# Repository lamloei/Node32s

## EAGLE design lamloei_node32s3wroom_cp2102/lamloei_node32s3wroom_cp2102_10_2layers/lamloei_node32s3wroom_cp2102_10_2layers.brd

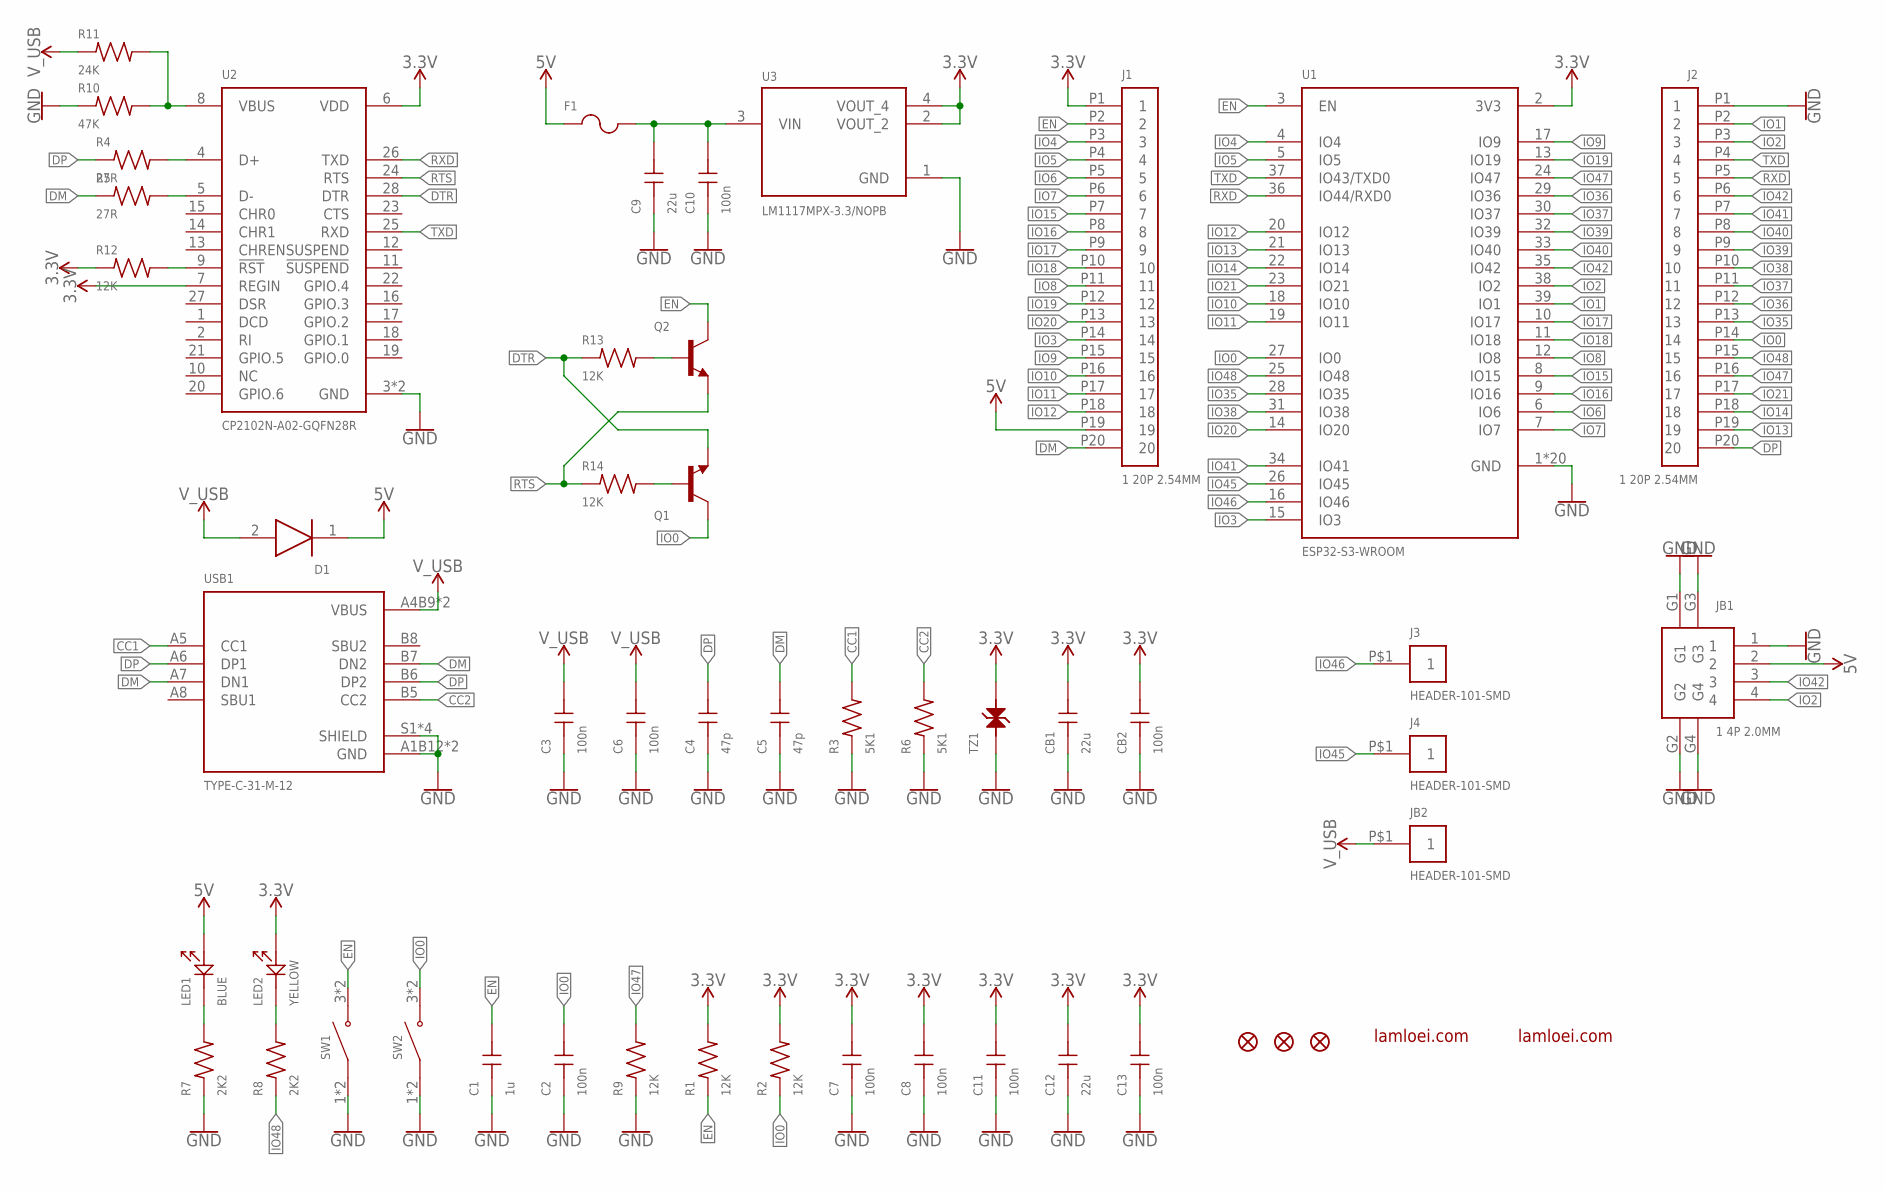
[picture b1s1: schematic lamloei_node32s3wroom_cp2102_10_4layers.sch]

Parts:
C1: 1u; GRM155R70J105KA12D
C2, C3, C6, C7, C8, C10, C11, C13: 100n; GCM155R71H104KE02D
C4, C5: 47p; GCM1555C1H470JA16D
C9, C12: 22u; GCM21BR71H105KA03L
CB1: 22u; GCM21BR71H105KA03L
CB2: 100n; GCM155R71H104KE02D
D1: PMEG4050EP,115
F1: MF-NSMF050-2
J1, J2: 1 20P 2.54MM; HEADER-120
J3, J4: HEADER-101-SMD
JB1: 1 4P 2.0MM; A2012WR-S-4P
JB2: HEADER-101-SMD
LED1: BLUE; 19-217BHC-ZL1M2RY3T
LED2: YELLOW; 19-213/Y2C-CQ2R2L/3T(CY)
Q1, Q2: BC847B,215
R1, R2, R9, R12, R13, R14: 12K; R0402
R3, R6: 5K1; R0402
R4, R5: 27R; R0402
R7, R8: 2K2; R0402
R10: 47K; R0402
R11: 24K; R0402
SW1, SW2: K2-1808SN-A4SW-01
TZ1: LXES15AAA1-153
U1: ESP32-S3-WROOM
U2: CP2102N-A02-GQFN28R
U3: LM1117MPX-3.3/NOPB
USB1: TYPE-C-31-M-12
ZFD1, ZFD2, ZFD3: FIDUCIAL1X2; FIDUCIAL-1X2
ZL1, ZL2: LAMLEOI_LOGO_3

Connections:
3.3V: C7.2, C8.2, C11.2, C12.2, C13.2, CB1.2, CB2.2, J1.P1 (1), LED2.2, R1.2, R2.2, R12.1, TZ1.2, U1.2 (3V3), U2.6 (VDD), U2.7 (REGIN), U3.2 (VOUT_2), U3.4 (VOUT_4); also elsewhere on the board
5V: D1.1 (K), F1.1, J1.P19 (19), JB1.2, LED1.2; also elsewhere on the board
CC1: R3.2, USB1.A5 (CC1)
CC2: R6.2, USB1.B5 (CC2)
DM: C5.2, J1.P20 (20), R5.1, USB1.A7 (DN1), USB1.B7 (DN2); also elsewhere on the board
DP: C4.2, J2.P20 (20), R4.1, USB1.A6 (DP1), USB1.B6 (DP2); also elsewhere on the board
DTR: Q1.E, R13.1, U2.28 (DTR)
EN: C1.2, J1.P2 (2), Q2.C, R1.1, SW1.3 (NO), SW1.4 (NO), U1.3 (EN); also elsewhere on the board
GND: C1.1, C2.1, C3.1, C4.1, C5.1, C6.1, C7.1, C8.1, C9.1, C10.1, C11.1, C12.1, C13.1, CB1.1, CB2.1, J2.P1 (1), JB1.1, JB1.G1, JB1.G2, JB1.G3, JB1.G4, R3.1, R6.1, R7.1, R9.1, R10.1, SW1.1 (COM), SW1.2 (COM), SW2.1 (COM), SW2.2 (COM), TZ1.1, U1.1 (GND), U1.1.1 (GND), U1.1.2 (GND), U1.1.3 (GND), U1.1.4 (GND), U1.1.5 (GND), U1.1.6 (GND), U1.1.7 (GND), U1.1.8 (GND), U1.1.9 (GND), U1.1.10 (GND), U1.1.11 (GND), U1.1.12 (GND), U1.1.13 (GND), U1.1.14 (GND), U1.1.15 (GND), U1.1.16 (GND), U1.1.17 (GND), U1.1.18 (GND), U1.40 (GND), U2.3 (GND), U2.29 (GND), U3.1 (GND), USB1.A1B12 (GND), USB1.B1A12 (GND), USB1.S1 (SHIELD), USB1.S2 (SHIELD), USB1.S3 (SHIELD), USB1.S4 (SHIELD); also elsewhere on the board
GPIO.5: U2.21 (GPIO.5)
IO0: C2.2, J2.P14 (14), Q1.C, R2.1, SW2.3 (NO), SW2.4 (NO), U1.27 (IO0); also elsewhere on the board
IO1: J2.P2 (2), U1.39 (IO1); also elsewhere on the board
IO2: J2.P3 (3), JB1.4, U1.38 (IO2); also elsewhere on the board
IO3: J1.P14 (14), U1.15 (IO3); also elsewhere on the board
IO4: J1.P3 (3), U1.4 (IO4); also elsewhere on the board
IO5: J1.P4 (4), U1.5 (IO5); also elsewhere on the board
IO6: J1.P5 (5), U1.6 (IO6); also elsewhere on the board
IO7: J1.P6 (6), U1.7 (IO7); also elsewhere on the board
IO8: J1.P11 (11), U1.12 (IO8); also elsewhere on the board
IO9: J1.P15 (15), U1.17 (IO9); also elsewhere on the board
IO10: J1.P16 (16), U1.18 (IO10); also elsewhere on the board
IO11: J1.P17 (17), U1.19 (IO11); also elsewhere on the board
IO12: J1.P18 (18), U1.20 (IO12); also elsewhere on the board
IO13: J2.P19 (19), U1.21 (IO13); also elsewhere on the board
IO14: J2.P18 (18), U1.22 (IO14); also elsewhere on the board
IO15: J1.P7 (7), U1.8 (IO15); also elsewhere on the board
IO16: J1.P8 (8), U1.9 (IO16); also elsewhere on the board
IO17: J1.P9 (9), U1.10 (IO17); also elsewhere on the board
IO18: J1.P10 (10), U1.11 (IO18); also elsewhere on the board
IO19: J1.P12 (12), U1.13 (IO19); also elsewhere on the board
IO20: J1.P13 (13), U1.14 (IO20); also elsewhere on the board
IO21: J2.P17 (17), U1.23 (IO21); also elsewhere on the board
IO35: J2.P13 (13), U1.28 (IO35); also elsewhere on the board
IO36: J2.P12 (12), U1.29 (IO36); also elsewhere on the board
IO37: J2.P11 (11), U1.30 (IO37); also elsewhere on the board
IO38: J2.P10 (10), U1.31 (IO38); also elsewhere on the board
IO39: J2.P9 (9), U1.32 (IO39); also elsewhere on the board
IO40: J2.P8 (8), U1.33 (IO40); also elsewhere on the board
IO41: J2.P7 (7), U1.34 (IO41); also elsewhere on the board
IO42: J2.P6 (6), JB1.3, U1.35 (IO42); also elsewhere on the board
IO45: J4.P$1, U1.26 (IO45)
IO46: J3.P$1, U1.16 (IO46)
IO47: J2.P16 (16), R9.2, U1.24 (IO47); also elsewhere on the board
IO48: J2.P15 (15), R8.1, U1.25 (IO48); also elsewhere on the board
unnamed: R5.2, U2.5 (D-)
unnamed: R4.2, U2.4 (D+)
unnamed: C9.2, C10.2, F1.2, U3.3 (VIN)
unnamed: LED1.1, R7.2
unnamed: LED2.1, R8.2
unnamed: Q2.B, R13.2
unnamed: Q1.B, R14.2
unnamed: R12.2, U2.9 (!RST)
unnamed: R10.2, R11.2, U2.8 (VBUS)
RTS: Q2.E, R14.1, U2.24 (RTS)
RXD: J2.P5 (5), U1.36 (IO44/RXD0), U2.26 (TXD); also elsewhere on the board
TXD: J2.P4 (4), U1.37 (IO43/TXD0), U2.25 (RXD); also elsewhere on the board
V_USB: C3.2, C6.2, D1.2 (A), JB2.P$1, R11.1, USB1.A4B9 (VBUS), USB1.B4A9 (VBUS)

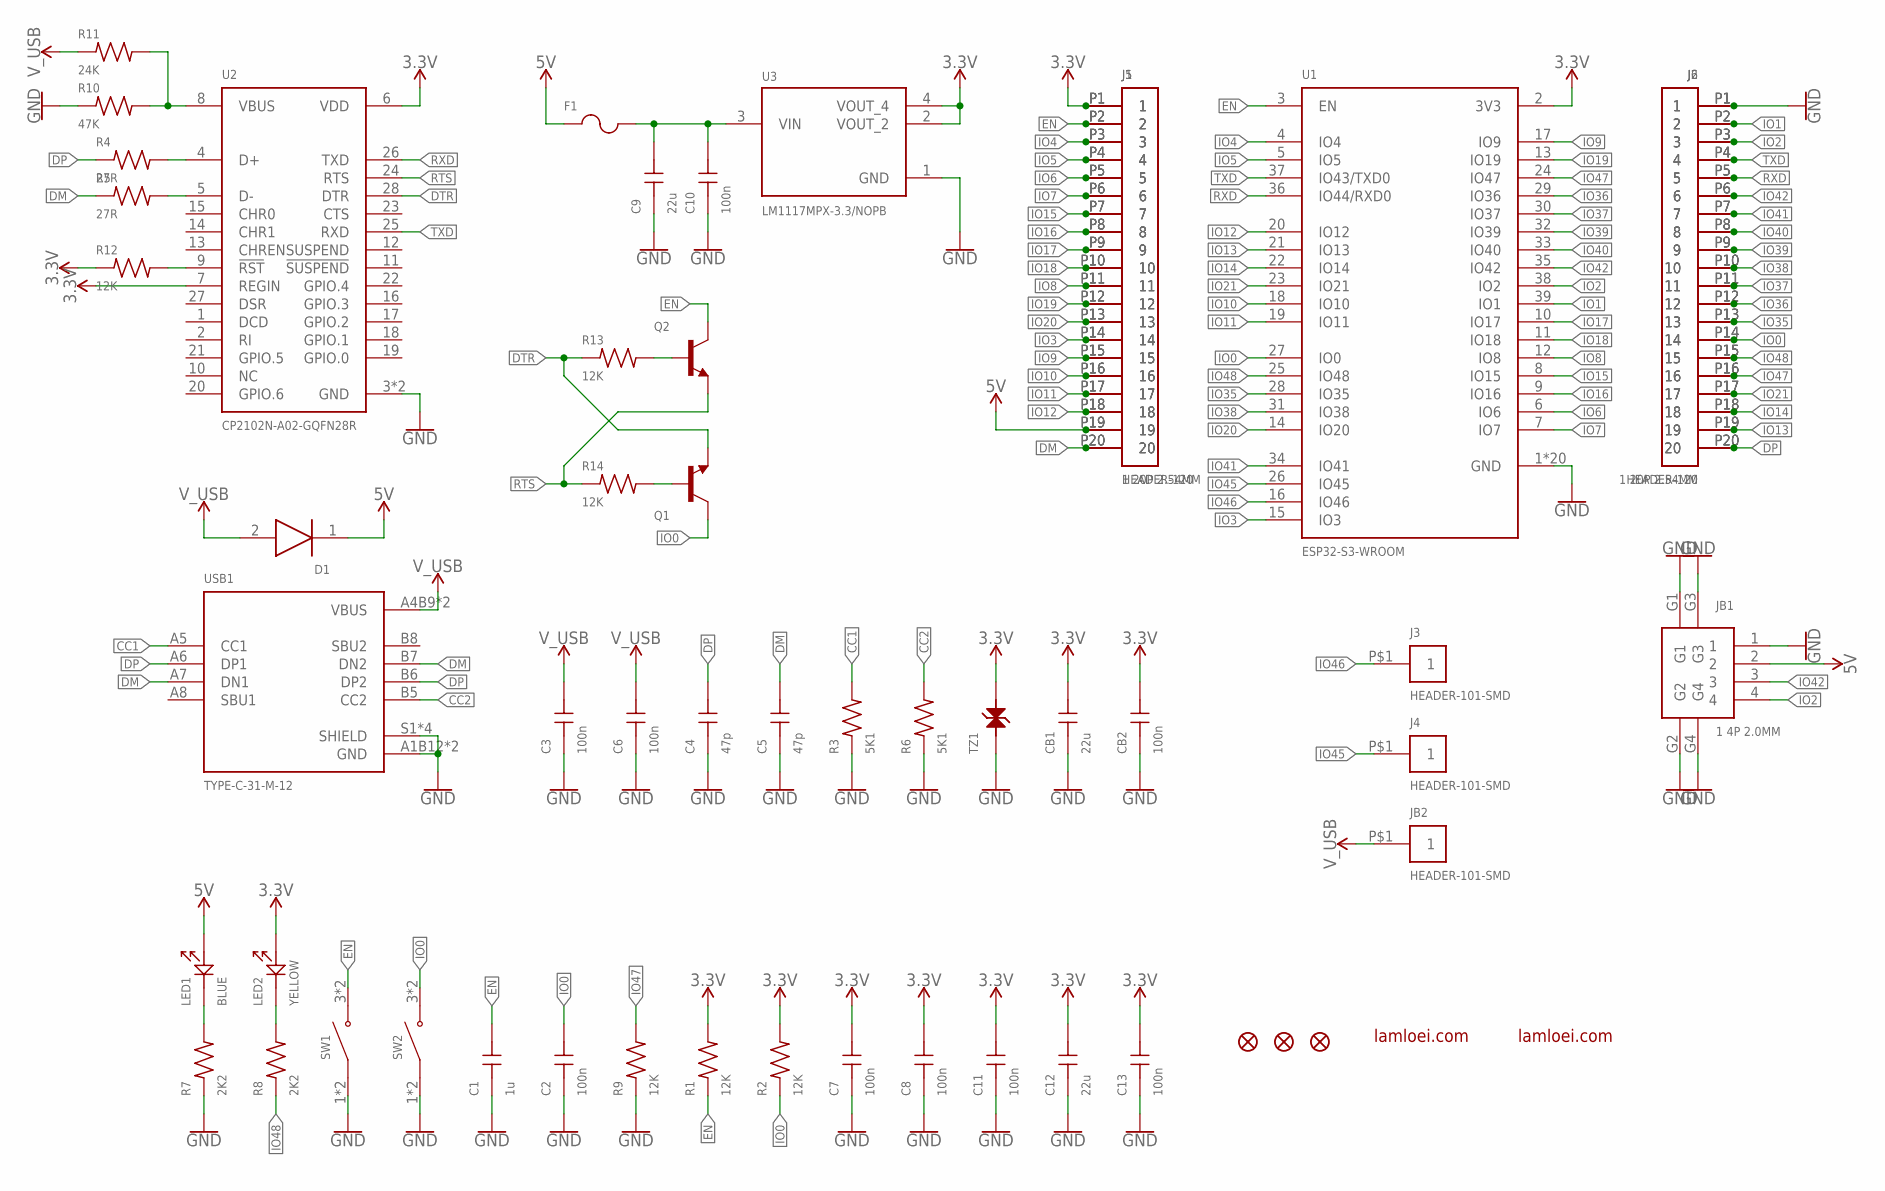
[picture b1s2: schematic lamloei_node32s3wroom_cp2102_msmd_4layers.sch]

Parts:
C1: 1u; GRM155R70J105KA12D
C2, C3, C6, C7, C8, C10, C11, C13: 100n; GCM155R71H104KE02D
C4, C5: 47p; GCM1555C1H470JA16D
C9, C12: 22u; GCM21BR71H105KA03L
CB1: 22u; GCM21BR71H105KA03L
CB2: 100n; GCM155R71H104KE02D
D1: PMEG4050EP,115
F1: MF-NSMF050-2
J1, J2: 1 20P 2.54MM; HEADER-120
J3, J4: HEADER-101-SMD
J5, J6: HEADER-120
JB1: 1 4P 2.0MM; A2012WR-S-4P
JB2: HEADER-101-SMD
LED1: BLUE; 19-217BHC-ZL1M2RY3T
LED2: YELLOW; 19-213/Y2C-CQ2R2L/3T(CY)
Q1, Q2: BC847B,215
R1, R2, R9, R12, R13, R14: 12K; R0402
R3, R6: 5K1; R0402
R4, R5: 27R; R0402
R7, R8: 2K2; R0402
R10: 47K; R0402
R11: 24K; R0402
SW1, SW2: K2-1808SN-A4SW-01
TZ1: LXES15AAA1-153
U1: ESP32-S3-WROOM
U2: CP2102N-A02-GQFN28R
U3: LM1117MPX-3.3/NOPB
USB1: TYPE-C-31-M-12
ZFD1, ZFD2, ZFD3: FIDUCIAL1X2; FIDUCIAL-1X2
ZL1, ZL2: LAMLEOI_LOGO_3

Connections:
3.3V: C7.2, C8.2, C11.2, C12.2, C13.2, CB1.2, CB2.2, J1.P1 (1), J5.P1 (1), LED2.2, R1.2, R2.2, R12.1, TZ1.2, U1.2 (3V3), U2.6 (VDD), U2.7 (REGIN), U3.2 (VOUT_2), U3.4 (VOUT_4)
5V: D1.1 (K), F1.1, J1.P19 (19), J5.P19 (19), JB1.2, LED1.2
CC1: R3.2, USB1.A5 (CC1)
CC2: R6.2, USB1.B5 (CC2)
DM: C5.2, J1.P20 (20), J5.P20 (20), R5.1, USB1.A7 (DN1), USB1.B7 (DN2)
DP: C4.2, J2.P20 (20), J6.P20 (20), R4.1, USB1.A6 (DP1), USB1.B6 (DP2)
DTR: Q1.E, R13.1, U2.28 (DTR)
EN: C1.2, J1.P2 (2), J5.P2 (2), Q2.C, R1.1, SW1.3 (NO), SW1.4 (NO), U1.3 (EN)
GND: C1.1, C2.1, C3.1, C4.1, C5.1, C6.1, C7.1, C8.1, C9.1, C10.1, C11.1, C12.1, C13.1, CB1.1, CB2.1, J2.P1 (1), J6.P1 (1), JB1.1, JB1.G1, JB1.G2, JB1.G3, JB1.G4, R3.1, R6.1, R7.1, R9.1, R10.1, SW1.1 (COM), SW1.2 (COM), SW2.1 (COM), SW2.2 (COM), TZ1.1, U1.1 (GND), U1.1.1 (GND), U1.1.2 (GND), U1.1.3 (GND), U1.1.4 (GND), U1.1.5 (GND), U1.1.6 (GND), U1.1.7 (GND), U1.1.8 (GND), U1.1.9 (GND), U1.1.10 (GND), U1.1.11 (GND), U1.1.12 (GND), U1.1.13 (GND), U1.1.14 (GND), U1.1.15 (GND), U1.1.16 (GND), U1.1.17 (GND), U1.1.18 (GND), U1.40 (GND), U2.3 (GND), U2.29 (GND), U3.1 (GND), USB1.A1B12 (GND), USB1.B1A12 (GND), USB1.S1 (SHIELD), USB1.S2 (SHIELD), USB1.S3 (SHIELD), USB1.S4 (SHIELD)
GPIO.5: U2.21 (GPIO.5)
IO0: C2.2, J2.P14 (14), J6.P14 (14), Q1.C, R2.1, SW2.3 (NO), SW2.4 (NO), U1.27 (IO0)
IO1: J2.P2 (2), J6.P2 (2), U1.39 (IO1)
IO2: J2.P3 (3), J6.P3 (3), JB1.4, U1.38 (IO2)
IO3: J1.P14 (14), J5.P14 (14), U1.15 (IO3)
IO4: J1.P3 (3), J5.P3 (3), U1.4 (IO4)
IO5: J1.P4 (4), J5.P4 (4), U1.5 (IO5)
IO6: J1.P5 (5), J5.P5 (5), U1.6 (IO6)
IO7: J1.P6 (6), J5.P6 (6), U1.7 (IO7)
IO8: J1.P11 (11), J5.P11 (11), U1.12 (IO8)
IO9: J1.P15 (15), J5.P15 (15), U1.17 (IO9)
IO10: J1.P16 (16), J5.P16 (16), U1.18 (IO10)
IO11: J1.P17 (17), J5.P17 (17), U1.19 (IO11)
IO12: J1.P18 (18), J5.P18 (18), U1.20 (IO12)
IO13: J2.P19 (19), J6.P19 (19), U1.21 (IO13)
IO14: J2.P18 (18), J6.P18 (18), U1.22 (IO14)
IO15: J1.P7 (7), J5.P7 (7), U1.8 (IO15)
IO16: J1.P8 (8), J5.P8 (8), U1.9 (IO16)
IO17: J1.P9 (9), J5.P9 (9), U1.10 (IO17)
IO18: J1.P10 (10), J5.P10 (10), U1.11 (IO18)
IO19: J1.P12 (12), J5.P12 (12), U1.13 (IO19)
IO20: J1.P13 (13), J5.P13 (13), U1.14 (IO20)
IO21: J2.P17 (17), J6.P17 (17), U1.23 (IO21)
IO35: J2.P13 (13), J6.P13 (13), U1.28 (IO35)
IO36: J2.P12 (12), J6.P12 (12), U1.29 (IO36)
IO37: J2.P11 (11), J6.P11 (11), U1.30 (IO37)
IO38: J2.P10 (10), J6.P10 (10), U1.31 (IO38)
IO39: J2.P9 (9), J6.P9 (9), U1.32 (IO39)
IO40: J2.P8 (8), J6.P8 (8), U1.33 (IO40)
IO41: J2.P7 (7), J6.P7 (7), U1.34 (IO41)
IO42: J2.P6 (6), J6.P6 (6), JB1.3, U1.35 (IO42)
IO45: J4.P$1, U1.26 (IO45)
IO46: J3.P$1, U1.16 (IO46)
IO47: J2.P16 (16), J6.P16 (16), R9.2, U1.24 (IO47)
IO48: J2.P15 (15), J6.P15 (15), R8.1, U1.25 (IO48)
unnamed: R5.2, U2.5 (D-)
unnamed: R4.2, U2.4 (D+)
unnamed: C9.2, C10.2, F1.2, U3.3 (VIN)
unnamed: LED1.1, R7.2
unnamed: LED2.1, R8.2
unnamed: Q2.B, R13.2
unnamed: Q1.B, R14.2
unnamed: R12.2, U2.9 (!RST)
unnamed: R10.2, R11.2, U2.8 (VBUS)
RTS: Q2.E, R14.1, U2.24 (RTS)
RXD: J2.P5 (5), J6.P5 (5), U1.36 (IO44/RXD0), U2.26 (TXD)
TXD: J2.P4 (4), J6.P4 (4), U1.37 (IO43/TXD0), U2.25 (RXD)
V_USB: C3.2, C6.2, D1.2 (A), JB2.P$1, R11.1, USB1.A4B9 (VBUS), USB1.B4A9 (VBUS)

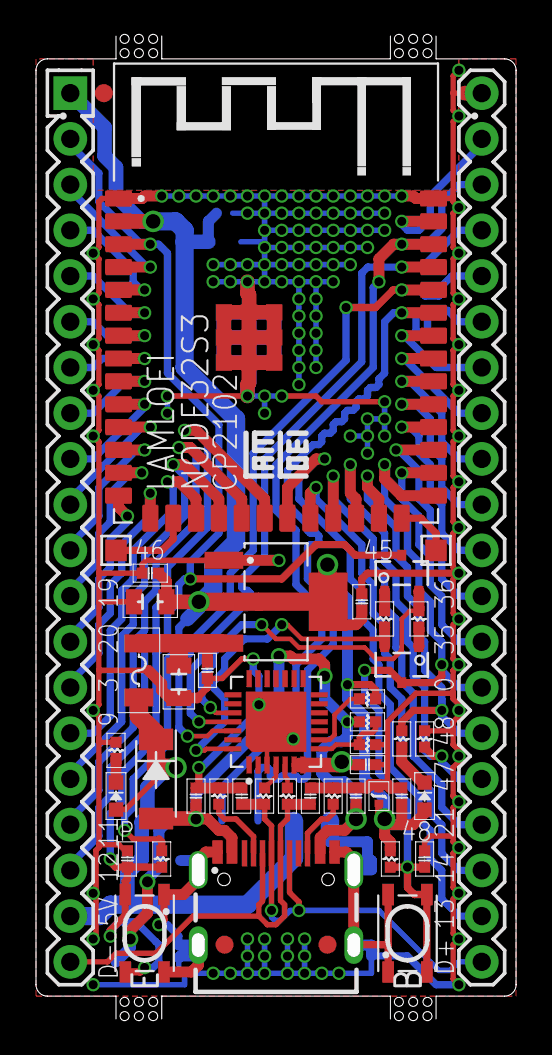
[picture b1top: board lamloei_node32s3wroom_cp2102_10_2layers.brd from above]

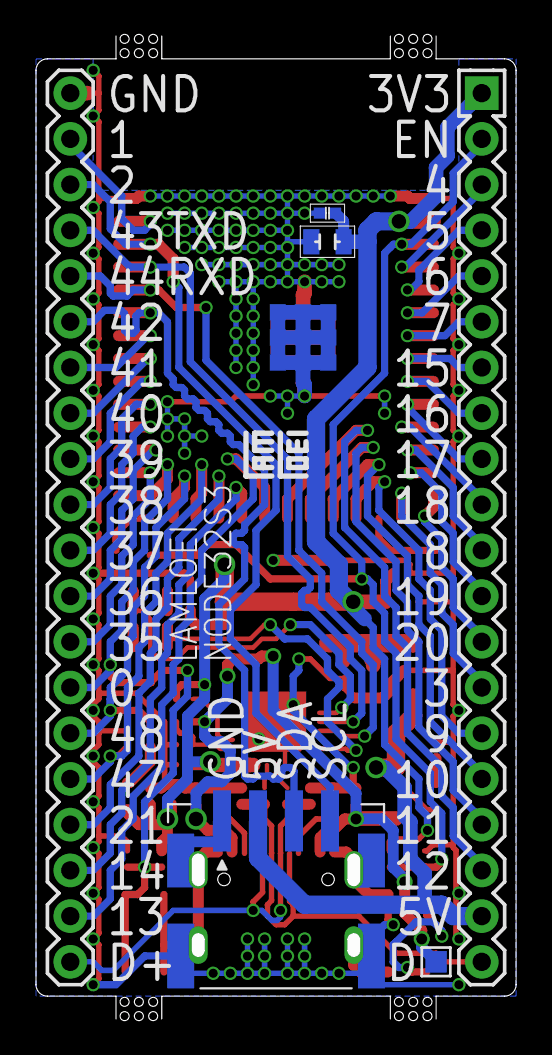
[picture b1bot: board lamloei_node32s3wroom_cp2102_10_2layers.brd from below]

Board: 2 copper layers, 26.7 x 54.6 mm, 53 parts (5 on the bottom side), 56 nets.

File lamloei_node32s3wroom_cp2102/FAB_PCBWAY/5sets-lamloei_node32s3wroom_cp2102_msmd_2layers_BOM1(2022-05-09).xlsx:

PCBWay Bom Quotation, Product No.:
Item # | *Designator | *Qty | *Mfg Part # | Description / Value | *Package/Footprint | Mounting Type | *Unit Price(5 sets) | *Total | *Delivery Time | *Actual Purchase Mfg Part # | *PCBWay Note | Customer Reply | PCBWay Update
1 | C1 | 1 | C52923 | Samsung - CL05A105KA5NQNC - 25V 1uF X5R ±10% | CAP_0402 | LCSC | 4.5999999999999999E-2 | 0.22999999999999998 |  | CL05A105KA5NQNC
2 | C2,C3,C6,C7,C8,C10,C11,C13 | 8 | C1525 | Samsung - CL05B104KO5NNNC - 16V 100nF X7R ±10% | CAP_0402 | LCSC | 3.0000000000000001E-3 | 0.12 |  | CL05B104KO5NNNC
3 | C4,C5 | 2 | C1567 | FH - 0402CG470J500NT - 50V 47pF C0G ±5% | CAP_0402 | LCSC | 1.2999999999999999E-2 | 0.13 |  | 0402CG470J500NT
4 | C9,C12 | 2 | C45783 | Samsung - CL21A226MAQNNNE - 25V 22UF X5R ±20% | CAP_0805 | LCSC | 6.6000000000000003E-2 | 0.66 |  | CL21A226MAQNNNE
5 | D1 | 1 | C456125 | Extended - Nexperia - PMEG4020EP,115 - 40V 490mV@2A 2A (SBD) | SOD-128 | LCSC | 0.29799999999999999 | 1.49 |  | PMEG4020EP,115
6 | F1 | 1 | C75464 | Extended - BOURNS - MF-NSMF050-2 - 13.2V 1A 1206 PTC | PTC_1206 | LCSC | 0.17699999999999999 | 0.88500000000000001 |  | MF-NSMF050-2
7 | LED1 | 1 | C72041 | Everlight Elec - 19-217/BHC-ZL1M2RY/3T - Blue 465~475nm 0603 (LED) | LED_0603 | LCSC | 0.1 | 0.5 |  | 19-217/BHC-ZL1M2RY/3T
8 | LED2 | 1 | C72038 | Everlight Elec - 19-213/Y2C-CQ2R2L/3T(CY) - Yellow 585.5~591.5nm 0603 (LED) | LED_0603 | LCSC | 0.13900000000000001 | 0.69500000000000006 |  | 19-213/Y2C-CQ2R2L/3T(CY)
9 | Q1,Q2 | 2 | C2146 | CJ - S8050 J3Y - Transistors NPN 500mA 25V | SOT-23-3 | LCSC | 0.128 | 1.28 |  | S8050 J3Y
10 | R1,R2,R9,R12,R13,R14 | 6 | C25752 | UNI-ROYAL - 0402WGF1202TCE - 12kΩ ±1% 1/16W | RES_0402 | LCSC | 3.0000000000000001E-3 | 9.0000000000000011E-2 |  | 0402WGF1202TCE
11 | R3,R6 | 2 | C25905 | UNI-ROYAL - 0402WGF5101TCE - 5.1kΩ ±1% 1/16W | RES_0402 | LCSC | 8.9999999999999993E-3 | 0.09 |  | 0402WGF5101TCE
12 | R4,R5 | 2 | C25092 | UNI-ROYAL - 0402WGF220JTCE - 22Ω ±1% 1/16W | RES_0402 | LCSC | 0.01 | 0.1 |  | 0402WGF220JTCE
13 | R7,R8 | 2 | C25879 | UNI-ROYAL - 0402WGF2201TCE - 2.2kΩ ±1% 1/16W | RES_0402 | LCSC | 8.0000000000000002E-3 | 0.08 |  | 0402WGF2201TCE
14 | R10 | 1 | C25792 | UNI-ROYAL - 0402WGF4702TCE - 47kΩ ±1% 1/16W | RES_0402 | LCSC | 1.7999999999999999E-2 | 0.09 |  | 0402WGF4702TCE
15 | R11 | 1 | C25769 | UNI-ROYAL - 0402WGF2402TCE - 24kΩ ±1% 1/16W | RES_0402 | LCSC | 1.7999999999999999E-2 | 0.09 |  | 0402WGF2402TCE
16 | SW1 | 1 | C145878 | Extended - Korean Hroparts Elec - K2-1808UN-A4SW-04 - SPST 50mA @ 12VDC | SMD-4_3.25x2.5x4.2P | LCSC | 0.28399999999999997 | 1.42 |  | K2-1808UN-A4SW-04
17 | SW2 | 1 | C283535 | Extended - Korean Hroparts Elec - K2-1808GN-A4SW-04 - SPST 50mA @ 12VDC | SMD-4_3.25x2.5x4.2P | LCSC | 0.31900000000000001 | 1.595 |  | K2-1808GN-A4SW-04
18 | TZ1 | 1 | C86141 | Extended - Murata - LXES15AAA1-153 - Diodes - ESD 0402 | TVS_0402 | LCSC | 0.127 | 0.63500000000000001 |  | LXES15AAA1-153
19 | U1 | 1 | 356-ESP3S3WRM2N32R8V | WiFi Modules - 802.11 [ENGINEERING SAMPLES] SMD Module | QFN-40_EP_18.0x25.5x1.27P | MOUSER |  |  |  | ESP32-S3-WROOM-2-N32R8V
20 | U2 | 1 | C964632 | SILICON LABS - CP2102N-A02-GQFN28R - Transceiver 1Mbps USB 1/1 | QFN-28_EP_5.0x5.0x0.5P |  |  |  |  | CP2102N-A02-GQFN28R
21 | U3 | 1 | C6186 | AMS - AMS1117-3.3 - 1A 1.3V@(800mA) Fixed 3.3V~3.3V Positive 1 (LDO) | SOT-223 |  |  |  |  | AMS1117-3.3
22 | USB1 | 1 | C165948 | Extended - Korean Hroparts Elec - TYPE-C-31-M-12 - USB - Type C Female | TYPE-C-31_L8.94_W7.3 | LCSC | 0.39800000000000002 | 1.9900000000000002 |  | TYPE-C-31-M-12
 |  |  |  |  |  |  | All Total | 12.17

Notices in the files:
parts and their libraries:
SparkFun-Aesthetics: Licensing: Creative Commons ShareAlike 4.0 International - https://creativecommons.org/licenses/by-sa/4.0
